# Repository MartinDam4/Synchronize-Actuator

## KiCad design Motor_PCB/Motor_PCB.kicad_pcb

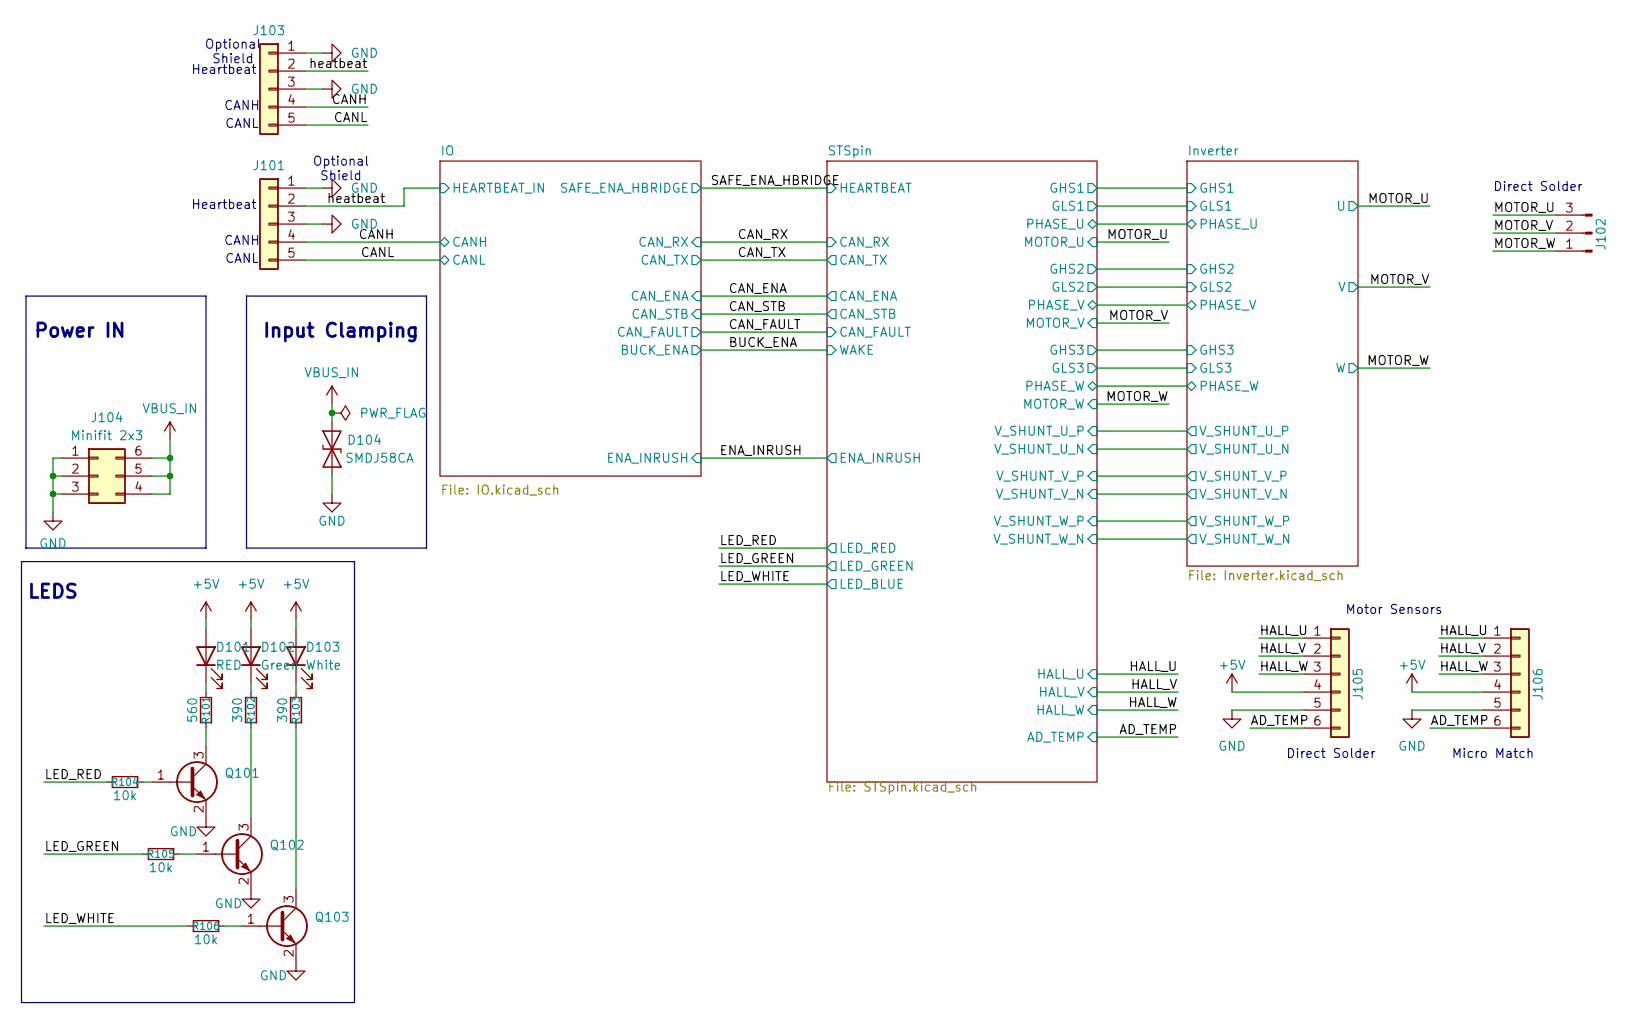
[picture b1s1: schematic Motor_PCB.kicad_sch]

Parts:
D101: RED; LED_0805_2012Metric
D102: Green; LED_0805_2012Metric
D103: White; LED_0805_2012Metric
D104: SMDJ58CA; D_SMC
J101, J103: Conn_01x05; 1411976
J102: Conn_01x03_Pin; SolderWire-1.5sqmm_1x03_P6mm_D1.7mm_OD3mm
J104: Minifit 2x3; Molex_Mini-Fit_Jr_5566-06A_2x03_P4.20mm_Vertical
J105: Conn_01x06; PinHeader_1x06_P1.27mm_Vertical
J106: Conn_01x06; CONN6_7-188275-6_TEC
Q101, Q102, Q103: MMBT3904; SOT-23
R101: 560; R_0603_1608Metric
R102, R103: 390; R_0603_1608Metric
R104, R105, R106: 10k; R_0603_1608Metric

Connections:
+5V: D101.2 (A), D102.2 (A), D103.2 (A), J105.4, J106.4; also elsewhere on the board
/AD_TEMP: J105.6, J106.6; also elsewhere on the board
/CANH: J101.4, J103.4; also elsewhere on the board
/CANL: J101.5, J103.5; also elsewhere on the board
/HALL_U: J105.1, J106.1; also elsewhere on the board
/HALL_V: J105.2, J106.2; also elsewhere on the board
/HALL_W: J105.3, J106.3; also elsewhere on the board
/LED_GREEN: R105.2; also elsewhere on the board
/LED_RED: R104.2; also elsewhere on the board
/LED_WHITE: R106.2; also elsewhere on the board
/MOTOR_U: J102.3; also elsewhere on the board
/MOTOR_V: J102.2; also elsewhere on the board
/MOTOR_W: J102.1; also elsewhere on the board
/heatbeat: J101.2, J103.2; also elsewhere on the board
GND: D104.1 (A1), J101.1, J101.3, J103.1, J103.3, J104.1, J104.2, J104.3, J105.5, J106.5, Q101.2 (E), Q102.2 (E), Q103.2 (E); also elsewhere on the board
unnamed: D101.1 (K), R101.2
unnamed: D102.1 (K), R102.2
unnamed: D103.1 (K), R103.2
unnamed: Q101.1 (B), R104.1
unnamed: Q101.3 (C), R101.1
unnamed: Q102.1 (B), R105.1
unnamed: Q102.3 (C), R102.1
unnamed: Q103.1 (B), R106.1
unnamed: Q103.3 (C), R103.1
VBUS_IN: D104.2 (A2), J104.4, J104.5, J104.6; also elsewhere on the board

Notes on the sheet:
CANH
Power IN
Heartbeat
Input Clamping
Micro Match
CANL
Direct Solder
LEDS
Optional Shield
Motor Sensors

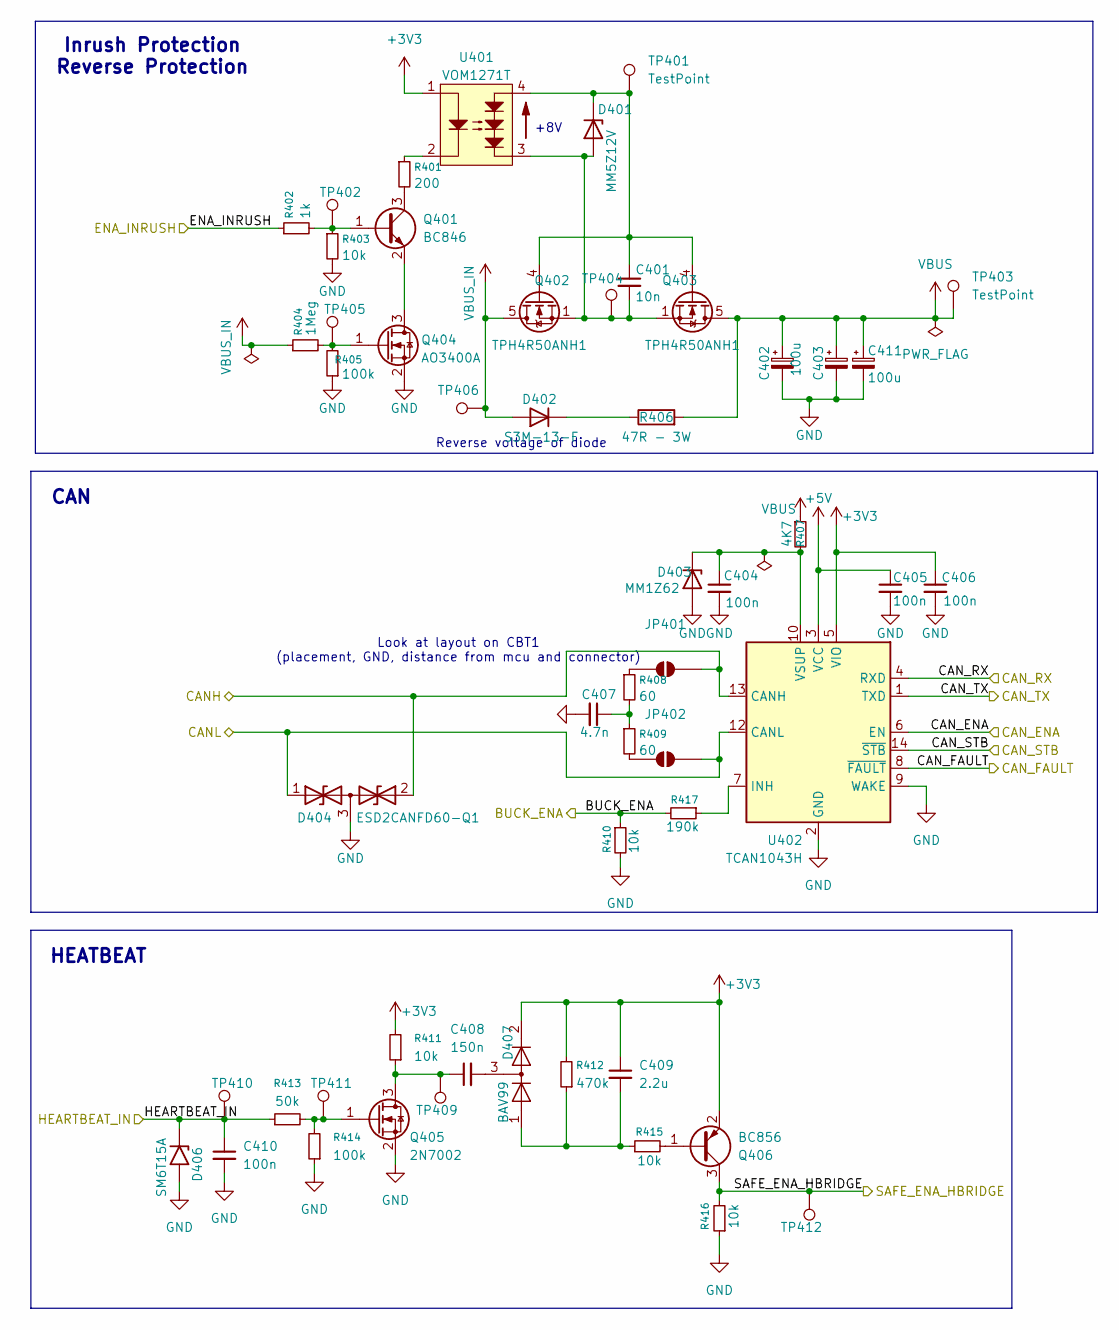
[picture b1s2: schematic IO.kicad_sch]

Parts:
C401: 10n; C_0603_1608Metric
C402, C403, C411: 100u; CP_Elec_10x10
C404, C405, C406, C410: 100n; C_0603_1608Metric
C407: 4.7n; C_0603_1608Metric
C408: 150n; C_0603_1608Metric
C409: 2.2u; C_0603_1608Metric
D401: MM5Z12V; D_SOD-523
D402: S3M-13-F; D_SMC
D403: MM1Z62; D_SOD-123
D404: ESD2CANFD60-Q1; SOT-23-3
D406: SM6T15A; D_SMB
D407: BAV99; SOT-23
JP401, JP402: SolderJumper_2_Open; SolderJumper-2_P1.3mm_Open_Pad1.0x1.5mm
Q401: BC846; SOT-23
Q402, Q403: TPH4R50ANH1; Infineon_PG-TDSON-8_6.15x5.15mm
Q404: AO3400A; SOT-23
Q405: 2N7002; SOT-23
Q406: BC856; SOT-23
R401: 200; R_0603_1608Metric
R402: 1k; R_0603_1608Metric
R403, R410, R411, R415, R416: 10k; R_0603_1608Metric
R404: 1Meg; R_0603_1608Metric
R405, R414: 100k; R_0603_1608Metric
R406: 47R - 3W; R_2512_6332Metric
R407: 4K7; R_0603_1608Metric
R408, R409: 60; R_0603_1608Metric
R412: 470k; R_0603_1608Metric
R413: 50k; R_0603_1608Metric
R417: 190k; R_0603_1608Metric
TP401, TP402, TP403, TP404, TP405, TP406, TP409, TP410, TP411, TP412: TestPoint; TestPoint_Pad_D1.5mm
U401: VOM1271T; SOP-4_VIS
U402: TCAN1043H; SOIC-14_3.9x8.7mm_P1.27mm

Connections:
+3V3: C406.1, C409.1, D407.2 (A), Q406.2 (E), R411.2, R412.2, U401.1, U402.5 (VIO); also elsewhere on the board
+5V: C405.1, U402.3 (VCC); also elsewhere on the board
/BUCK_ENA: R410.1, R417.2; also elsewhere on the board
/CANH: D404.2 (A2), JP401.2 (B), U402.13 (CANH); also elsewhere on the board
/CANL: D404.1 (A1), JP402.2 (B), U402.12 (CANL); also elsewhere on the board
/CAN_ENA: U402.6 (EN); also elsewhere on the board
/CAN_FAULT: U402.8 (~FAULT); also elsewhere on the board
/CAN_RX: U402.4 (RXD); also elsewhere on the board
/CAN_STB: U402.14 (~STB); also elsewhere on the board
/CAN_TX: U402.1 (TXD); also elsewhere on the board
/ENA_INRUSH: R402.1; also elsewhere on the board
/SAFE_ENA_HBRIDGE: Q406.3 (C), R416.2, TP412.1 (1_1); also elsewhere on the board
/heatbeat: C410.1, D406.1 (A1), R413.1, TP410.1 (1_1); also elsewhere on the board
GND: C402.2, C403.2, C404.2, C405.2, C406.2, C407.2, C410.2, C411.2, D403.2 (A), D404.3 (common), D406.2 (A2), Q404.2 (S), Q405.2 (S), R403.2, R405.1, R410.2, R414.1, R416.1, U402.2 (GND), U402.9 (WAKE); also elsewhere on the board
unnamed: C407.1, R408.2, R409.1
unnamed: C408.2, D407.3 (K)
unnamed: C409.2, D407.1 (K), R412.1, R415.1
unnamed: C401.2, D401.2 (A), Q402.1 (S), Q402.2 (S), Q402.3 (S), Q403.1 (S), Q403.2 (S), Q403.3 (S), TP404.1 (1_1), U401.3
unnamed: C401.1, D401.1 (K), Q402.4 (G), Q403.4 (G), TP401.1 (1_1), U401.4
unnamed: D402.1 (K), R406.1
unnamed: C404.1, D403.1 (K), R407.2, U402.10 (VSUP)
unnamed: JP401.1 (A), R408.1
unnamed: JP402.1 (A), R409.2
unnamed: Q401.1 (B), R402.2, R403.1, TP402.1 (1_1)
unnamed: Q401.3 (C), R401.2
unnamed: Q401.2 (E), Q404.3 (D)
unnamed: Q404.1 (G), R404.2, R405.2, TP405.1 (1_1)
unnamed: C408.1, Q405.3 (D), R411.1, TP409.1 (1_1)
unnamed: Q405.1 (G), R413.2, R414.2, TP411.1 (1_1)
unnamed: Q406.1 (B), R415.2
unnamed: R401.1, U401.2
unnamed: R417.1, U402.7 (INH)
VBUS: C402.1, C403.1, C411.1, Q403.5 (D), R406.2, R407.1, TP403.1 (1_1); also elsewhere on the board
VBUS_IN: D402.2 (A), Q402.5 (D), R404.1, TP406.1 (1_1); also elsewhere on the board

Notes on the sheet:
Reverse voltage of diode
+8V
HEATBEAT
Look at layout on CBT1 (placement, GND, distance from mcu and connector)
CAN
Inrush Protection Reverse Protection

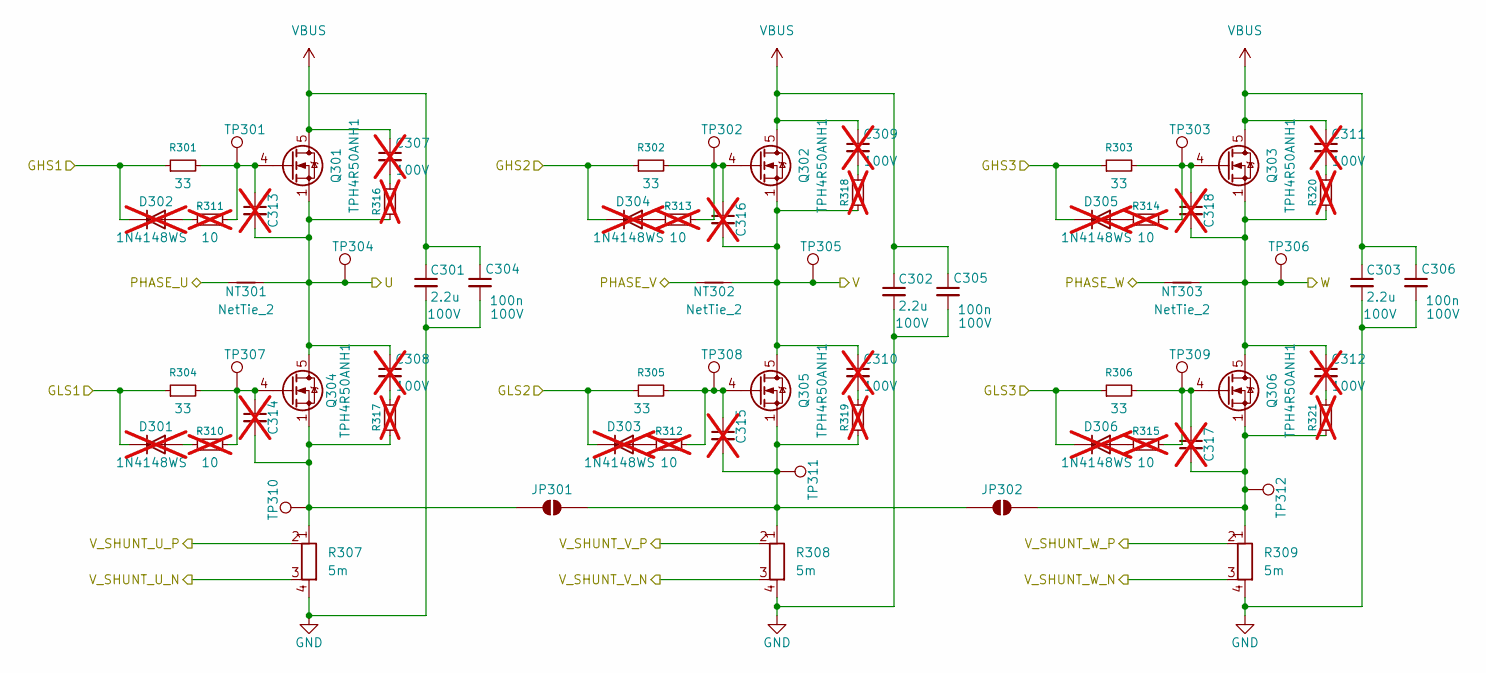
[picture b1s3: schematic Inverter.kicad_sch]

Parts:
C301, C302, C303: 2.2u; C_1210_3225Metric
C304, C305, C306: 100n; C_0603_1608Metric
C307, C308, C309, C310, C311, C312: C_0805_2012Metric; not fitted
C313, C314, C315, C316, C317, C318: C_Small; C_0805_2012Metric; not fitted
D301, D302, D303, D304, D305, D306: 1N4148WS; D_SOD-323; not fitted
JP301, JP302: SolderJumper_2_Open; SolderJumper-2P_Open_Pad_4.5x2.5mm
NT301, NT302, NT303: NetTie_2; NetTie-2_SMD_Pad0.5mm
Q301, Q302, Q303, Q304, Q305, Q306: TPH4R50ANH1; Infineon_PG-TDSON-8_6.15x5.15mm
R301, R302, R303, R304, R305, R306: 33; R_0603_1608Metric
R307, R308, R309: 5m; R_2512_Shunt
R310, R311, R312, R313, R314, R315: 10; R_0603_1608Metric; not fitted
R316, R317, R318, R319, R320, R321: R_0805_2012Metric; not fitted
TP301, TP302, TP303, TP304, TP305, TP306, TP307, TP308, TP309, TP310, TP311, TP312: TestPoint; TestPoint_Pad_D1.5mm

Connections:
/Inverter/GHS1: D302.1 (K), R301.1; also elsewhere on the board
/Inverter/GHS2: D304.1 (K), R302.1; also elsewhere on the board
/Inverter/GHS3: D305.1 (K), R303.1; also elsewhere on the board
/Inverter/GLS1: D301.1 (K), R304.1; also elsewhere on the board
/Inverter/GLS2: D303.1 (K), R305.1; also elsewhere on the board
/Inverter/GLS3: D306.1 (K), R306.1; also elsewhere on the board
/Inverter/V_SHUNT_U_N: R307.3; also elsewhere on the board
/Inverter/V_SHUNT_U_P: R307.2; also elsewhere on the board
/Inverter/V_SHUNT_V_N: R308.3; also elsewhere on the board
/Inverter/V_SHUNT_V_P: R308.2; also elsewhere on the board
/Inverter/V_SHUNT_W_N: R309.3; also elsewhere on the board
/Inverter/V_SHUNT_W_P: R309.2; also elsewhere on the board
/MOTOR_U: C308.1, C313.2, NT301.2, Q301.1 (S), Q301.2 (S), Q301.3 (S), Q304.5 (D), R316.1, TP304.1 (1_1); also elsewhere on the board
/MOTOR_V: C310.1, C316.2, NT302.2, Q302.1 (S), Q302.2 (S), Q302.3 (S), Q305.5 (D), R318.1, TP305.1 (1_1); also elsewhere on the board
/MOTOR_W: C312.1, C318.2, NT303.2, Q303.1 (S), Q303.2 (S), Q303.3 (S), Q306.5 (D), R320.1, TP306.1 (1_1); also elsewhere on the board
/STSpin/PHASE_U: NT301.1; also elsewhere on the board
/STSpin/PHASE_V: NT302.1; also elsewhere on the board
/STSpin/PHASE_W: NT303.1; also elsewhere on the board
GND: C301.2, C302.2, C303.2, C304.2, C305.2, C306.2, R307.4, R308.4, R309.4; also elsewhere on the board
unnamed: C307.2, R316.2
unnamed: C308.2, R317.2
unnamed: C309.2, R318.2
unnamed: C310.2, R319.2
unnamed: C311.2, R320.2
unnamed: C312.2, R321.2
unnamed: D301.2 (A), R310.1
unnamed: D302.2 (A), R311.1
unnamed: D303.2 (A), R312.1
unnamed: D304.2 (A), R313.1
unnamed: D305.2 (A), R314.1
unnamed: D306.2 (A), R315.1
unnamed: C314.2, JP301.1 (A), Q304.1 (S), Q304.2 (S), Q304.3 (S), R307.1, R317.1, TP310.1 (1_1)
unnamed: C315.2, JP301.2 (B), JP302.1 (A), Q305.1 (S), Q305.2 (S), Q305.3 (S), R308.1, R319.1, TP311.1 (1_1)
unnamed: C317.2, JP302.2 (B), Q306.1 (S), Q306.2 (S), Q306.3 (S), R309.1, R321.1, TP312.1 (1_1)
unnamed: C313.1, Q301.4 (G), R301.2, R311.2, TP301.1 (1_1)
unnamed: C316.1, Q302.4 (G), R302.2, R313.2, TP302.1 (1_1)
unnamed: C318.1, Q303.4 (G), R303.2, R314.2, TP303.1 (1_1)
unnamed: C314.1, Q304.4 (G), R304.2, R310.2, TP307.1 (1_1)
unnamed: C315.1, Q305.4 (G), R305.2, R312.2, TP308.1 (1_1)
unnamed: C317.1, Q306.4 (G), R306.2, R315.2, TP309.1 (1_1)
VBUS: C301.1, C302.1, C303.1, C304.1, C305.1, C306.1, C307.1, C309.1, C311.1, Q301.5 (D), Q302.5 (D), Q303.5 (D); also elsewhere on the board

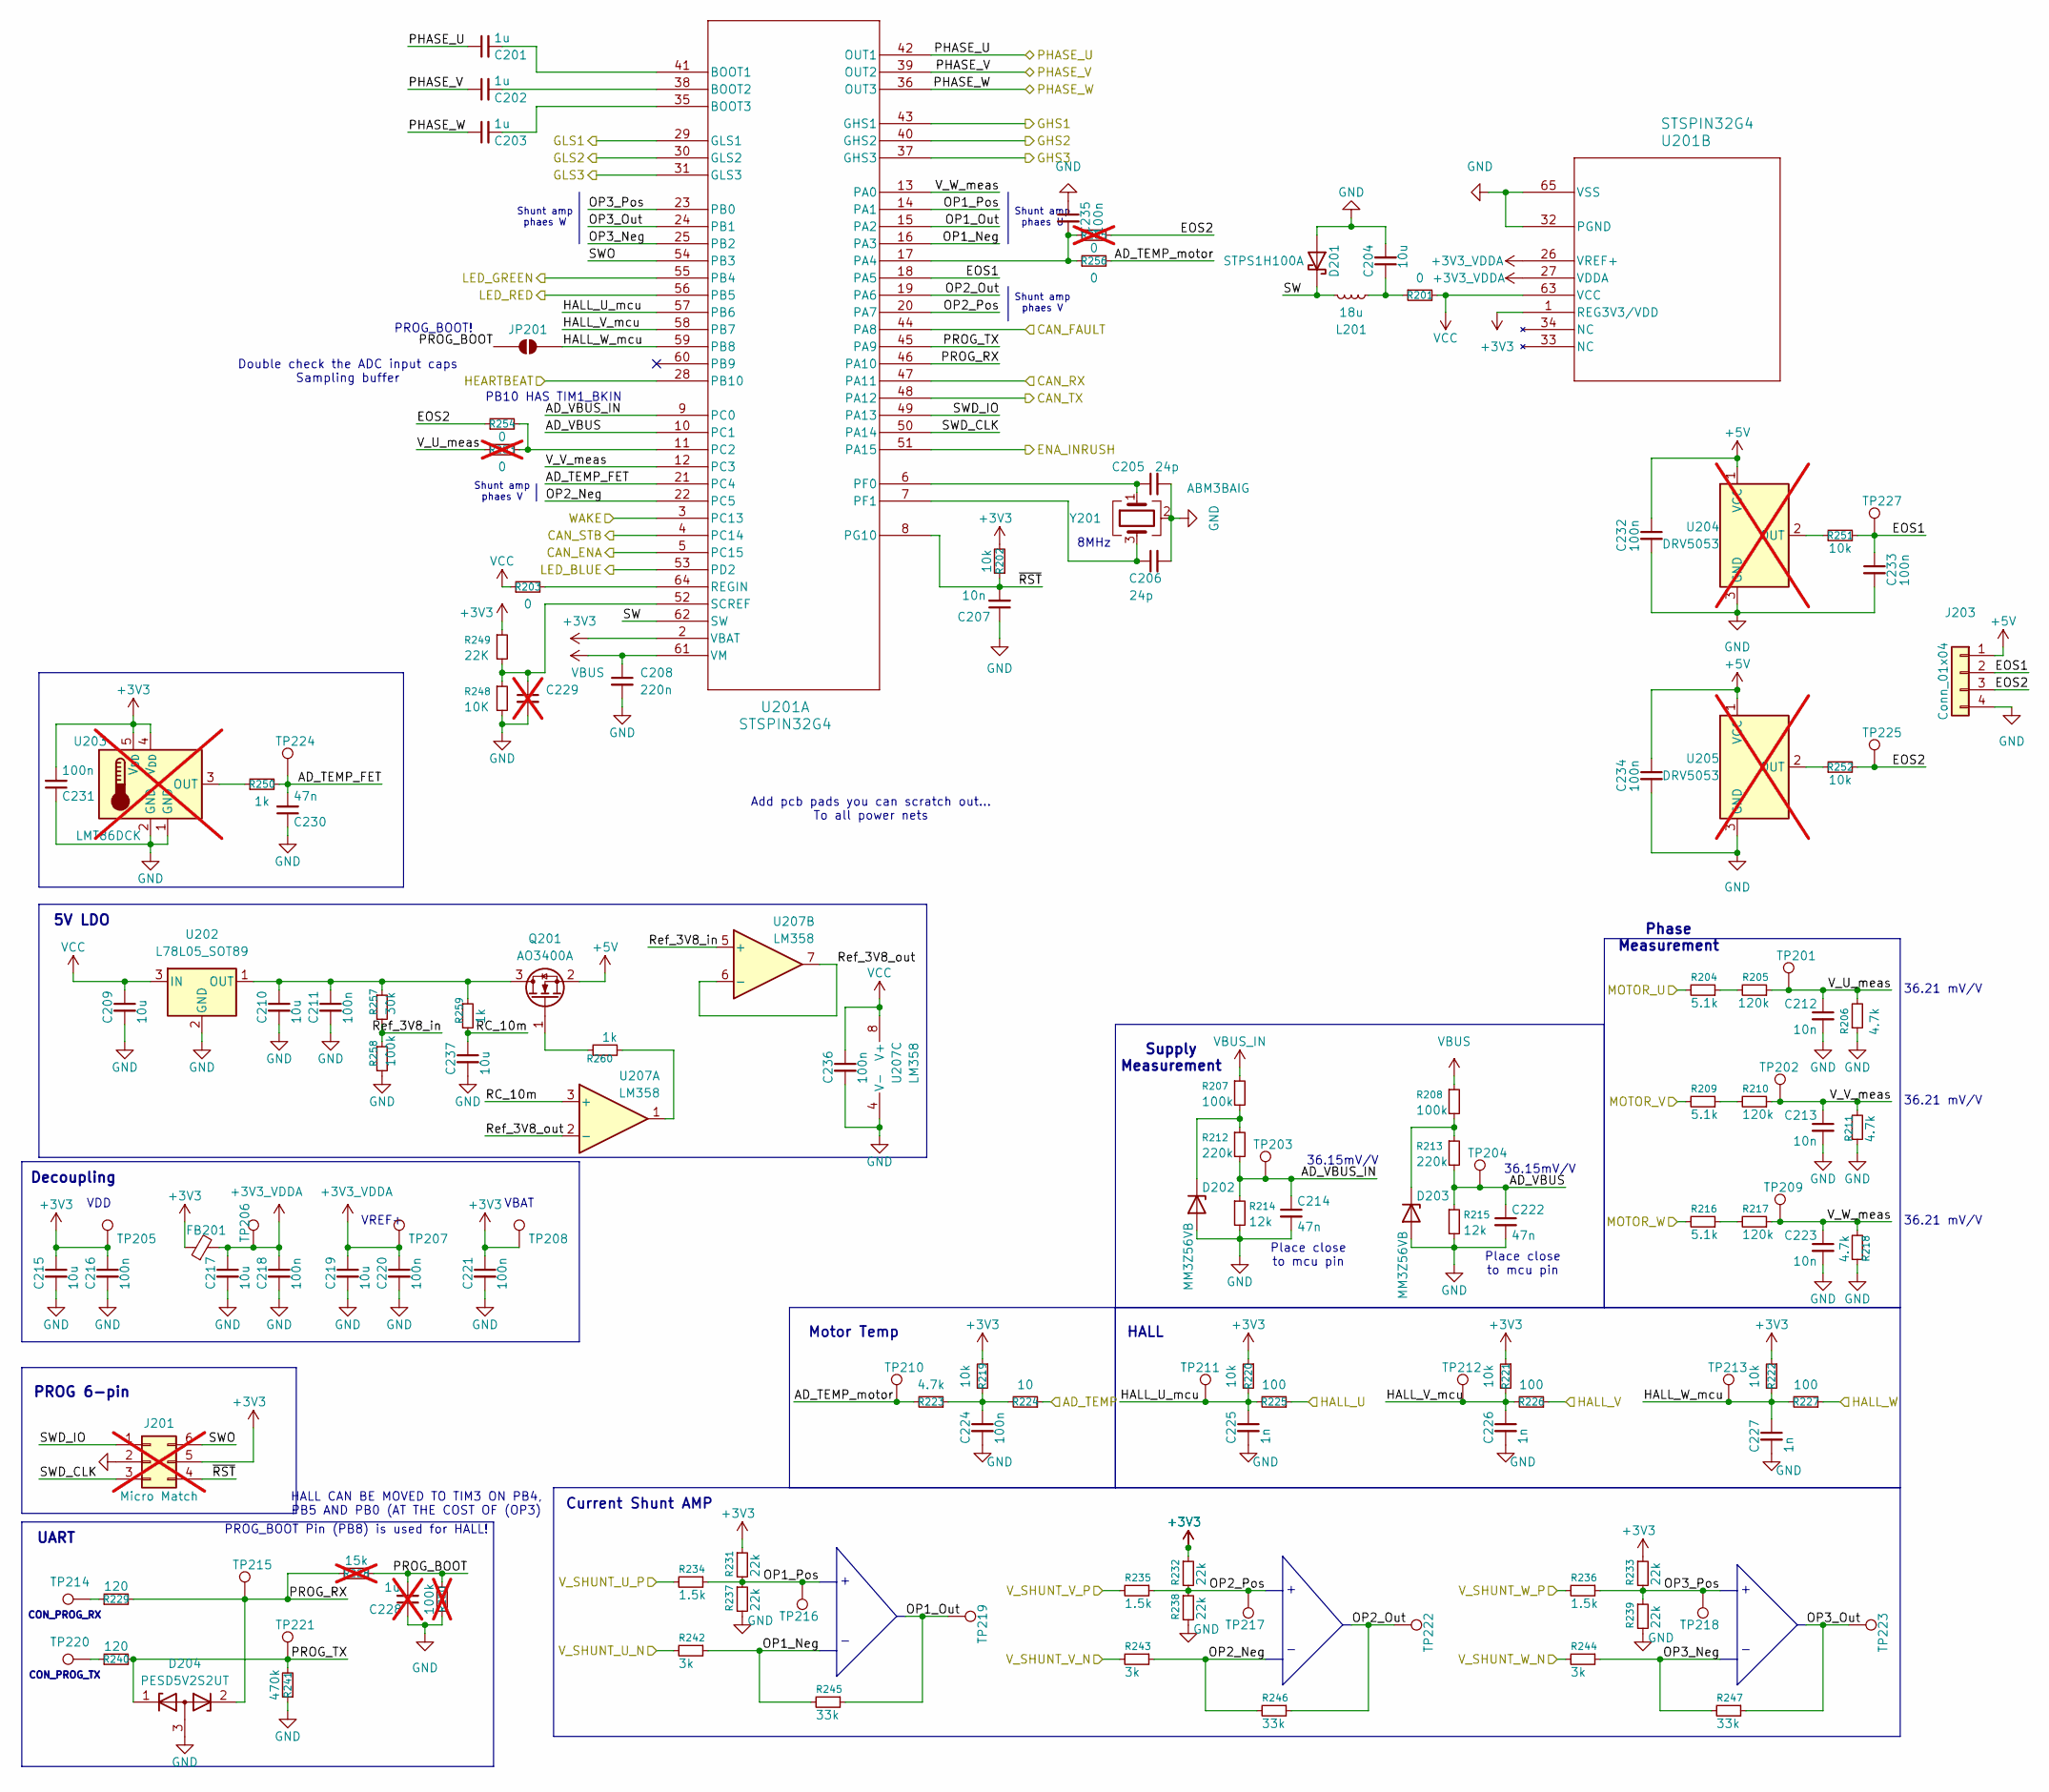
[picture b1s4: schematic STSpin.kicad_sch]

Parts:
C201, C202, C203: 1u; C_0805_2012Metric
C204, C237: 10u; C_0603_1608Metric
C205, C206: 24p; C_0603_1608Metric
C207, C212, C213, C223: 10n; C_0603_1608Metric
C208: 220n; C_0603_1608Metric
C209, C210, C215, C217, C219: 10u; C_0805_2012Metric
C211, C216, C218, C220, C221, C224, C231, C232, C233, C234, C235, C236: 100n; C_0603_1608Metric
C214, C222, C230: 47n; C_0603_1608Metric
C225, C226, C227: 1n; C_0603_1608Metric
C228: 1u; C_0603_1608Metric; not fitted
C229: 220n; C_0603_1608Metric; not fitted
D201: STPS1H100A; D_SMA
D202, D203: MM3Z56VB; D_SOD-323F
D204: PESD5V2S2UT; SOT-23
FB201: FerriteBead_Small; L_0603_1608Metric
J201: Micro Match; CONN6_7-188275-6_TEC; not fitted
J203: Conn_01x04; PinHeader_1x04_P2.54mm_Vertical
JP201: SolderJumper_2_Open; SolderJumper-2_P1.3mm_Open_Pad1.0x1.5mm
L201: 18u; L_APV_ANR4020
Q201: AO3400A; SOT-23
R201, R203, R254, R256: 0; R_0603_1608Metric
R202, R219, R220, R221, R222, R251, R252: 10k; R_0603_1608Metric
R204, R209, R216: 5.1k; R_0603_1608Metric
R205, R210, R217: 120k; R_0603_1608Metric
R206, R211, R218, R223: 4.7k; R_0603_1608Metric
R207, R208, R258: 100k; R_0603_1608Metric
R212, R213: 220k; R_0603_1608Metric
R214, R215: 12k; R_0603_1608Metric
R224: 10; R_0603_1608Metric
R225, R226, R227: 100; R_0603_1608Metric
R228: 15k; R_0603_1608Metric; not fitted
R229, R240: 120; R_0603_1608Metric
R230: 100k; R_0603_1608Metric; not fitted
R231, R232, R233, R237, R238, R239: 22k; R_0603_1608Metric
R234, R235, R236: 1.5k; R_0603_1608Metric
R241: 470k; R_0603_1608Metric
R242, R243, R244: 3k; R_0603_1608Metric
R245, R246, R247: 33k; R_0603_1608Metric
R248: 10K; R_0603_1608Metric
R249: 22K; R_0603_1608Metric
R250, R259, R260: 1k; R_0603_1608Metric
R253, R255: 0; R_0603_1608Metric; not fitted
R257: 30k; R_0603_1608Metric
TP201, TP202, TP203, TP204, TP205, TP206, TP207, TP208, TP209, TP210, TP211, TP212, TP213, TP214, TP215, TP216, TP217, TP218, TP219, TP220, TP221, TP222, TP223, TP224, TP225, TP227: TestPoint; TestPoint_Pad_D1.5mm
U201: STSPIN32G4; QFN_IN32G4_STM
U202: L78L05_SOT89; SOT-89-3
U203: LMT86DCK; SOT-353_SC-70-5; not fitted
U204, U205: DRV5053; SOT-23; not fitted
U207: LM358; SOIC-8_3.9x4.9mm_P1.27mm
Y201: ABM3BAIG; Crystal_SMD_5032-4Pin_5.0x3.2mm

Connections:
+3V3: C215.1, C216.1, C221.1, C231.2, FB201.1, J201.5, R202.2, R219.1, R220.1, R221.1, R222.1, R231.1, R232.1, R233.1, R249.1, TP205.1 (1_1), TP208.1 (1_1), U201.1 (REG3V3/VDD), U201.2 (VBAT), U203.4 (V_{DD}), U203.5 (V_{DD}); also elsewhere on the board
+3V3_VDDA: C217.1, C218.1, C219.1, C220.1, FB201.2, TP206.1 (1_1), TP207.1 (1_1), U201.26 (VREF+), U201.27 (VDDA)
+5V: C232.1, C234.1, J203.1, Q201.2 (S), U204.1 (VCC), U205.1 (VCC); also elsewhere on the board
/AD_TEMP: R224.1; also elsewhere on the board
/BUCK_ENA: U201.3 (PC13); also elsewhere on the board
/CAN_ENA: U201.5 (PC15); also elsewhere on the board
/CAN_FAULT: U201.44 (PA8); also elsewhere on the board
/CAN_RX: U201.47 (PA11); also elsewhere on the board
/CAN_STB: U201.4 (PC14); also elsewhere on the board
/CAN_TX: U201.48 (PA12); also elsewhere on the board
/ENA_INRUSH: U201.51 (PA15); also elsewhere on the board
/HALL_U: R225.1; also elsewhere on the board
/HALL_V: R226.1; also elsewhere on the board
/HALL_W: R227.1; also elsewhere on the board
/Inverter/GHS1: U201.43 (GHS1); also elsewhere on the board
/Inverter/GHS2: U201.40 (GHS2); also elsewhere on the board
/Inverter/GHS3: U201.37 (GHS3); also elsewhere on the board
/Inverter/GLS1: U201.29 (GLS1); also elsewhere on the board
/Inverter/GLS2: U201.30 (GLS2); also elsewhere on the board
/Inverter/GLS3: U201.31 (GLS3); also elsewhere on the board
/Inverter/V_SHUNT_U_N: R242.2; also elsewhere on the board
/Inverter/V_SHUNT_U_P: R234.2; also elsewhere on the board
/Inverter/V_SHUNT_V_N: R243.2; also elsewhere on the board
/Inverter/V_SHUNT_V_P: R235.2; also elsewhere on the board
/Inverter/V_SHUNT_W_N: R244.2; also elsewhere on the board
/Inverter/V_SHUNT_W_P: R236.2; also elsewhere on the board
/LED_GREEN: U201.55 (PB4); also elsewhere on the board
/LED_RED: U201.56 (PB5); also elsewhere on the board
/LED_WHITE: U201.53 (PD2); also elsewhere on the board
/MOTOR_U: R204.2; also elsewhere on the board
/MOTOR_V: R209.2; also elsewhere on the board
/MOTOR_W: R216.2; also elsewhere on the board
/SAFE_ENA_HBRIDGE: U201.28 (PB10); also elsewhere on the board
/STSpin/AD_TEMP_FET: C230.2, R250.2, TP224.1 (1_1), U201.21 (PC4)
/STSpin/AD_TEMP_motor: R223.2, R256.2, TP210.1 (1_1)
/STSpin/AD_VBUS: C222.1, R213.2, R215.1, TP204.1 (1_1), U201.10 (PC1)
/STSpin/AD_VBUS_IN: C214.1, R212.2, R214.1, TP203.1 (1_1), U201.9 (PC0)
/STSpin/EOS1: C233.1, J203.2, R251.2, TP227.1 (1_1), U201.18 (PA5)
/STSpin/EOS2: J203.3, R252.2, R254.1, R255.2, TP225.1 (1_1)
/STSpin/HALL_U_mcu: C225.1, R220.2, R225.2, TP211.1 (1_1), U201.57 (PB6)
/STSpin/HALL_V_mcu: C226.1, R221.2, R226.2, TP212.1 (1_1), U201.58 (PB7)
/STSpin/HALL_W_mcu: C227.1, JP201.2 (B), R222.2, R227.2, TP213.1 (1_1), U201.59 (PB8)
/STSpin/OP1_Neg: R242.1, R245.2, U201.16 (PA3)
/STSpin/OP1_Out: R245.1, TP219.1 (1_1), U201.15 (PA2)
/STSpin/OP1_Pos: R231.2, R234.1, R237.1, TP216.1 (1_1), U201.14 (PA1)
/STSpin/OP2_Neg: R243.1, R246.2, U201.22 (PC5)
/STSpin/OP2_Out: R246.1, TP222.1 (1_1), U201.19 (PA6)
/STSpin/OP2_Pos: R232.2, R235.1, R238.1, TP217.1 (1_1), U201.20 (PA7)
/STSpin/OP3_Neg: R244.1, R247.2, U201.25 (PB2)
/STSpin/OP3_Out: R247.1, TP223.1 (1_1), U201.24 (PB1)
/STSpin/OP3_Pos: R233.2, R236.1, R239.1, TP218.1 (1_1), U201.23 (PB0)
/STSpin/PHASE_U: C201.1, U201.42 (OUT1); also elsewhere on the board
/STSpin/PHASE_V: C202.1, U201.39 (OUT2); also elsewhere on the board
/STSpin/PHASE_W: C203.1, U201.36 (OUT3); also elsewhere on the board
/STSpin/PROG_BOOT: C228.2, JP201.1 (A), R228.2, R230.2
/STSpin/PROG_RX: D204.2 (K), R228.1, R229.2, TP215.1 (1_1), U201.46 (PA10)
/STSpin/PROG_TX: D204.1 (K), R240.2, R241.2, TP221.1 (1_1), U201.45 (PA9)
/STSpin/RC_10m: C237.1, R259.2, U207.3 (+)
/STSpin/Ref_3V8_in: R257.2, R258.1, U207.5 (+)
/STSpin/Ref_3V8_out: U207.2 (-), U207.6 (-), U207.7
/STSpin/SW: D201.1 (K), L201.1, U201.62 (SW)
/STSpin/SWD_CLK: J201.3, U201.50 (PA14)
/STSpin/SWD_IO: J201.1, U201.49 (PA13)
/STSpin/SWO: J201.6, U201.54 (PB3)
/STSpin/V_U_meas: C212.1, R205.1, R206.2, R253.1, TP201.1 (1_1)
/STSpin/V_V_meas: C213.1, R210.1, R211.2, TP202.1 (1_1), U201.12 (PC3)
/STSpin/V_W_meas: C223.1, R217.1, R218.2, TP209.1 (1_1), U201.13 (PA0)
/STSpin/~RST: C207.2, J201.4, R202.1, U201.8 (PG10)
GND: C204.2, C205.2, C206.2, C207.1, C208.2, C209.2, C210.2, C211.2, C212.2, C213.2, C214.2, C215.2, C216.2, C217.2, C218.2, C219.2, C220.2, C221.2, C222.2, C223.2, C224.2, C225.2, C226.2, C227.2, C228.1, C229.2, C230.1, C231.1, C232.2, C233.2, C234.2, C235.1, C236.2, C237.2, D201.2 (A), D202.2 (A), D203.2 (A), D204.3 (A), J201.2, J203.4, R206.1, R211.1, R214.2, R215.2, R218.1, R230.1, R237.2, R238.2, R239.2, R241.1, R248.2, R258.2, U201.32 (PGND), U201.65 (VSS), U202.2 (GND), U203.1 (GND), U203.2 (GND), U204.3 (GND), U205.3 (GND), U207.4 (V-), Y201.2 (G), Y201.4 (G); also elsewhere on the board
unnamed: C204.1, L201.2, R201.1
unnamed: C224.1, R219.2, R223.1, R224.2
unnamed: D202.1 (K), R207.2, R212.1
unnamed: D203.1 (K), R208.2, R213.1
unnamed: C210.1, C211.1, Q201.3 (D), R257.1, R259.1, U202.1 (OUT)
unnamed: Q201.1 (G), R260.1
unnamed: R204.1, R205.2
unnamed: R209.1, R210.2
unnamed: R216.1, R217.2
unnamed: R229.1, TP214.1 (1_1)
unnamed: R240.1, TP220.1 (1_1)
unnamed: R260.2, U207.1
unnamed: C201.2, U201.41 (BOOT1)
unnamed: C202.2, U201.38 (BOOT2)
unnamed: C203.2, U201.35 (BOOT3)
unnamed: C235.2, R255.1, R256.1, U201.17 (PA4)
unnamed: R253.2, R254.2, U201.11 (PC2)
unnamed: C205.1, U201.6 (PF0), Y201.1
unnamed: C206.1, U201.7 (PF1), Y201.3
unnamed: R203.2, U201.64 (REGIN)
unnamed: C229.1, R248.1, R249.2, U201.52 (SCREF)
unnamed: R250.1, U203.3 (OUT)
unnamed: R251.1, U204.2 (OUT)
unnamed: R252.1, U205.2 (OUT)
VBUS: C208.1, R208.1, U201.61 (VM); also elsewhere on the board
VBUS_IN: R207.1; also elsewhere on the board
VCC: C209.1, C236.1, R201.2, R203.1, U201.63 (VCC), U202.3 (IN), U207.8 (V+)

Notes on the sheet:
5V LDO
36.21 mV/V
CON_PROG_TX
Supply Measurement
CON_PROG_RX
Current Shunt AMP
Add pcb pads you can scratch out... To all power nets
HALL CAN BE MOVED TO TIM3 ON PB4, PB5 AND PB0 (AT THE COST OF (OP3)
Shunt amp phaes V
36.15mV/V
PROG 6-pin
Place close to mcu pin
PB10 HAS TIM1_BKIN
Motor Temp
Double check the ADC input caps Sampling buffer
8MHz
PROG_BOOT Pin (PB8) is used for HALL!
Shunt amp phaes W
HALL
Shunt amp phaes U
UART
Phase Measurement
VBAT
Decoupling
PROG_BOOT!
VREF+
VDD

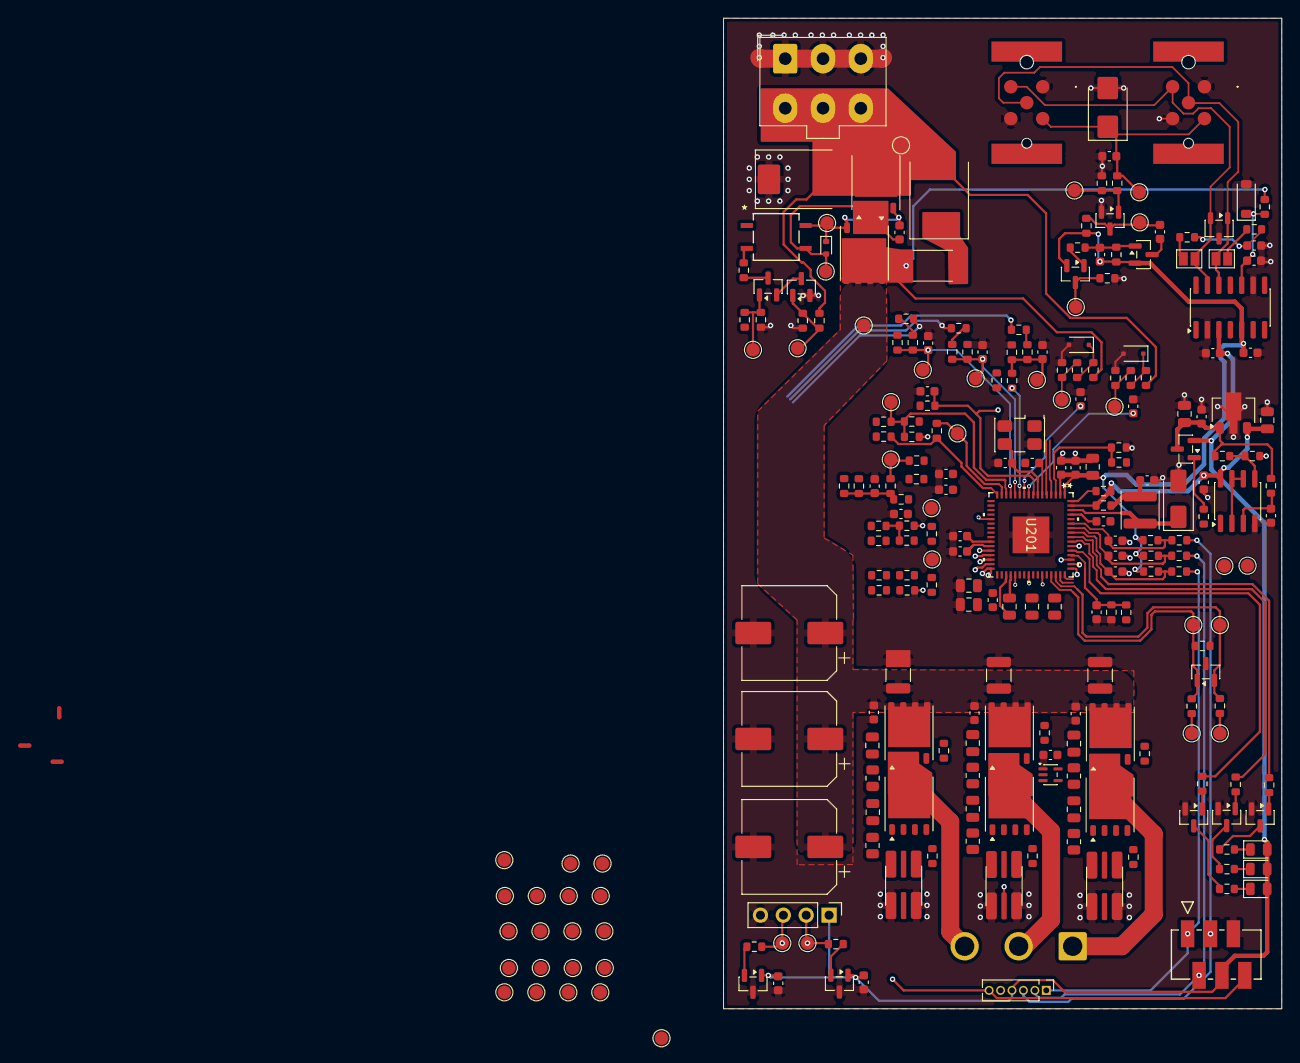
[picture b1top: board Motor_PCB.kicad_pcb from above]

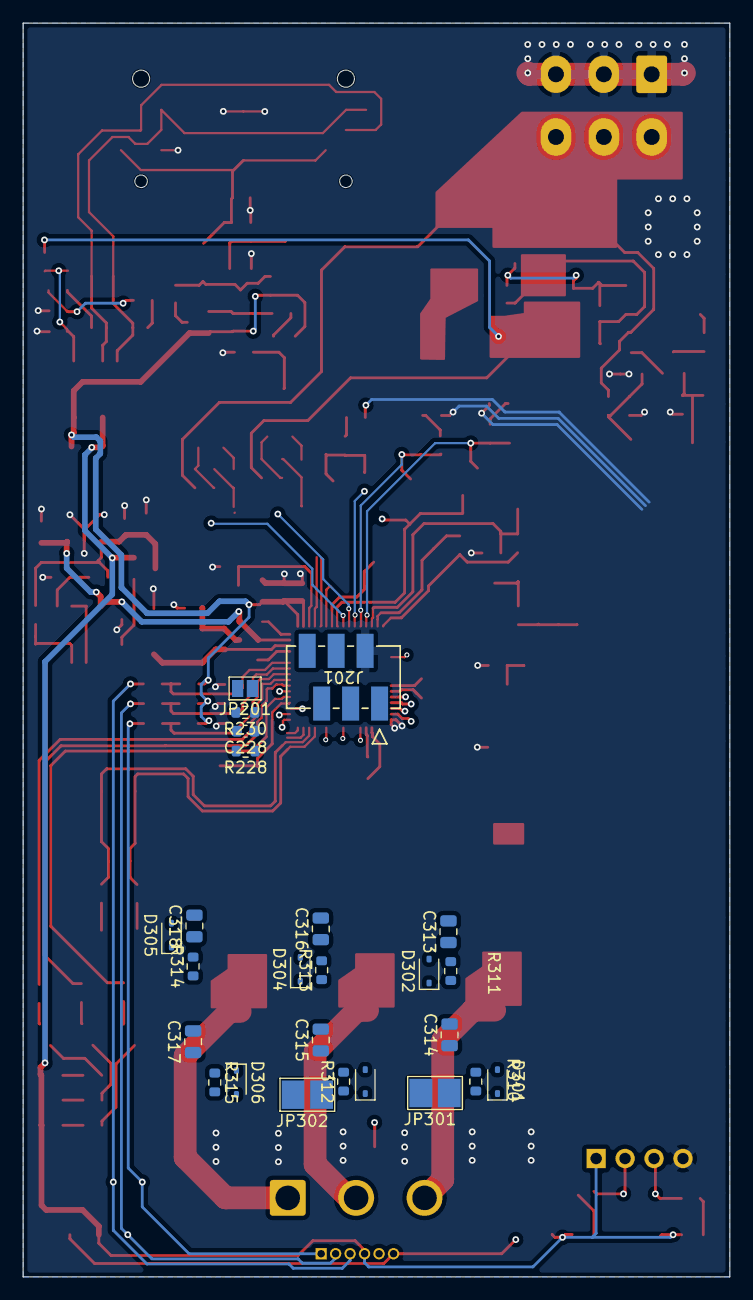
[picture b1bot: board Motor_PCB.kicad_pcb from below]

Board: 4 copper layers, 62.0 x 110.0 mm, 281 parts (25 on the bottom side), 147 nets.
